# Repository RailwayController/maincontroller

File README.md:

<!--
SPDX-FileCopyrightText: 2022 Sidings Media <contact@sidingsmedia.com>
SPDX-License-Identifier: CC-BY-SA-4.0
-->

# Railway Controller - Main control board

The main control board is the central control node of the railway controller
system. The main control board controls all aspects of the system, from handling
user inputs to sending commands to the control nodes.

The board is based upon the RP2040 and can either be fitted with a Raspberry Pi
Pico board or use the RP2040 chip on it's own with all the required supporting
circuitry being implemented on the board it's self. The board is designed to fit
inside a standard 3U eurocard enclosure with a depth of 160mm and a height of
100mm. The rear connector provides connectivity to the backplane to allow
communication between all nodes in the rack as well as to supply power to the
board.

The PCBs have been designed with 2 layers and with SMD components that should be
possible to hand solder with a small tip and some practice. An important note,
the boards have been designed acording to JLCPCB's design constraints, if you
are ordering from a different manufacturer, it is a good idea to make sure that
they support the same or better constraints.

This repository contains designs for the main controller board for
use with the railway controller system. Rendered versions of the schematics, for
example schematics in the PDF format, are included with the releases. Gerber
files are also included with releases. These have been generated to work with
JLCPCB but they should work with most other board manufacturers. 

## Licence
This repo uses the [REUSE](https://reuse.software) standard in order to
communicate the correct licence for the file. For those unfamiliar with
the standard the licence for each file can be found in one of three
places. The licence will either be in a comment block at the top of the
file, in a `.license` file with the same name as the file, or in the
dep5 file located in the `.reuse` directory. If you are unsure of the
licencing terms please contact
[contact@sidingsmedia.com](mailto:contact@sidingsmedia.com?subject=Railway%20Controller%20Licence).
All files committed to this repo must contain valid licencing
information or the pull request can not be accepted.

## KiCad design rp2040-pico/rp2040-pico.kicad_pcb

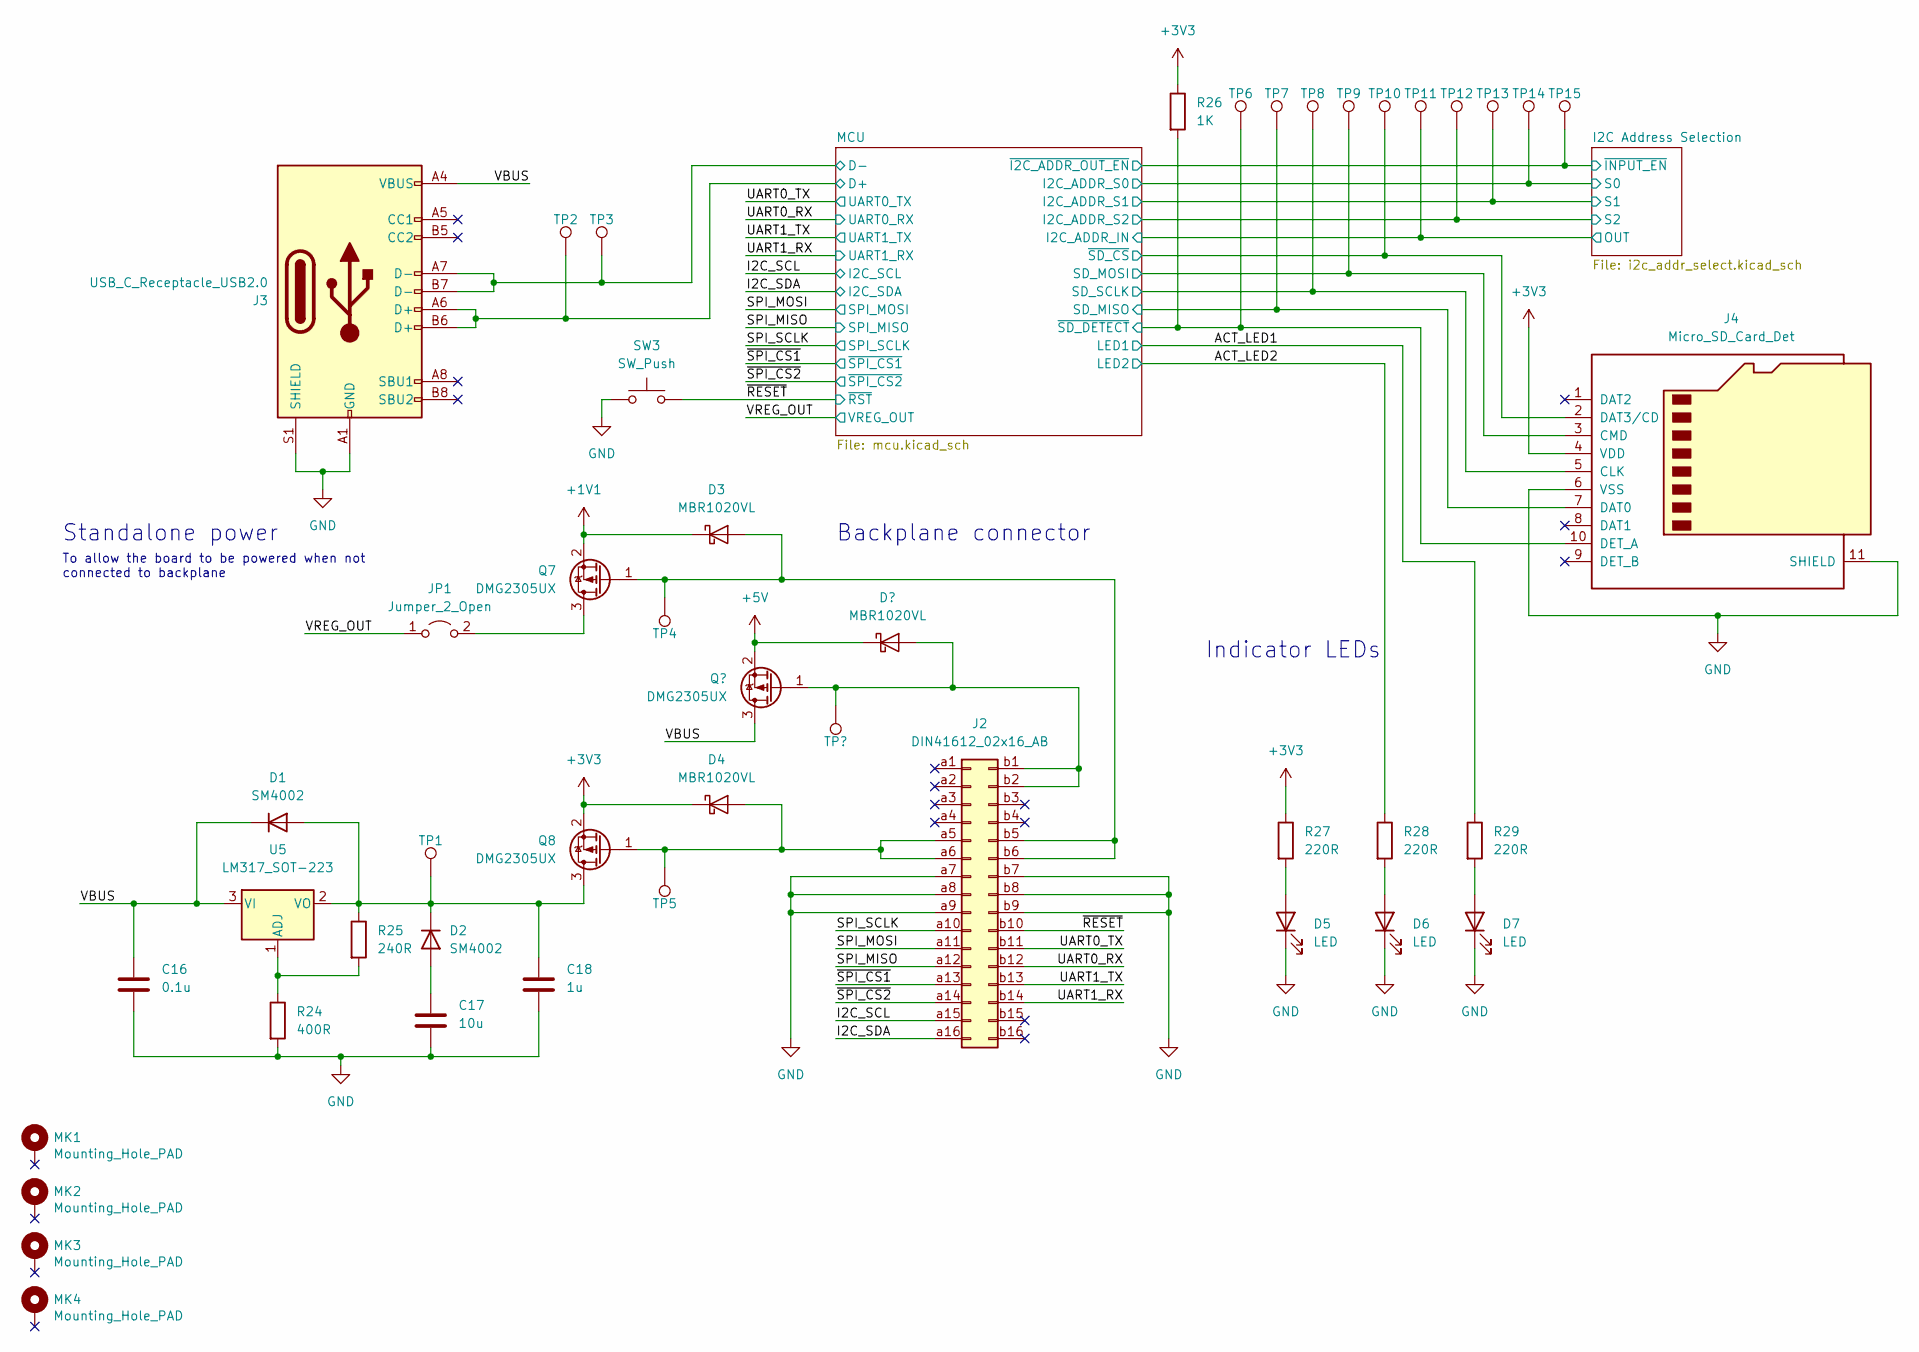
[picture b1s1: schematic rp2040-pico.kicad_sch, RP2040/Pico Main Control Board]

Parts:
C16: 0.1u; C_0402_1005Metric_Pad0.74x0.62mm_HandSolder
C17: 10u; C_0402_1005Metric_Pad0.74x0.62mm_HandSolder
C18: 1u; C_0402_1005Metric_Pad0.74x0.62mm_HandSolder
D1, D2: SM4002; D_MELF
D3, D4: MBR1020VL; D_SOD-123F
D5, D6, D7: LED; LED_0603_1608Metric_Pad1.05x0.95mm_HandSolder
J2: DIN41612_02x16_AB; DIN41612_B2_2x16_Male_Horizontal_THT
J3: USB_C_Receptacle_USB2.0; USB_C_Receptacle_Palconn_UTC16-G
J4: Micro_SD_Card_Det; microSD_HC_Molex_104031-0811
JP1: Jumper_2_Open; SolderJumper-2_P1.3mm_Open_Pad1.0x1.5mm
MK1, MK2, MK3, MK4: Mounting_Hole_PAD; MountingHole_2.7mm
Q7, Q8: DMG2305UX; SOT-23
R24: 400R; R_0402_1005Metric_Pad0.72x0.64mm_HandSolder
R25: 240R; R_0402_1005Metric_Pad0.72x0.64mm_HandSolder
R26: 1K; R_0402_1005Metric_Pad0.72x0.64mm_HandSolder
R27, R28, R29: 220R; R_0402_1005Metric_Pad0.72x0.64mm_HandSolder
SW3: SW_Push; SW_SPST_B3U-1000P
TP1, TP2, TP3, TP4, TP5, TP6, TP7, TP8, TP9, TP10, TP11, TP12, TP13, TP14, TP15: TestPoint; TestPoint_Pad_D1.0mm
U5: LM317_SOT-223; SOT-223-3_TabPin2

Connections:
+1V1: D3.1 (K), Q7.2 (S); also elsewhere on the board
+3V3: D4.1 (K), J4.4 (VDD), Q8.2 (S), R26.1, R27.1; also elsewhere on the board
/ACT_LED1: R29.1; also elsewhere on the board
/ACT_LED2: R28.1; also elsewhere on the board
/I2C Address Selection/OUT: TP11.1; also elsewhere on the board
/I2C Address Selection/S0: TP14.1; also elsewhere on the board
/I2C Address Selection/S1: TP13.1; also elsewhere on the board
/I2C Address Selection/S2: TP12.1; also elsewhere on the board
/I2C Address Selection/~INPUT_EN: TP15.1; also elsewhere on the board
/I2C_SCL: J2.a15; also elsewhere on the board
/I2C_SDA: J2.a16; also elsewhere on the board
/MCU/D+: J3.A6 (D+), J3.B6 (D+), TP2.1; also elsewhere on the board
/MCU/D-: J3.A7 (D-), J3.B7 (D-), TP3.1; also elsewhere on the board
/MCU/SD_MISO: J4.7 (DAT0), TP7.1; also elsewhere on the board
/MCU/SD_MOSI: J4.3 (CMD), TP9.1; also elsewhere on the board
/MCU/SD_SCLK: J4.5 (CLK), TP8.1; also elsewhere on the board
/MCU/~SD_CS: J4.2 (DAT3/CD), TP10.1; also elsewhere on the board
/MCU/~SD_DETECT: J4.10 (DET_A), R26.2, TP6.1; also elsewhere on the board
/SPI_MISO: J2.a12; also elsewhere on the board
/SPI_MOSI: J2.a11; also elsewhere on the board
/SPI_SCLK: J2.a10; also elsewhere on the board
/UART0_RX: J2.b12; also elsewhere on the board
/UART0_TX: J2.b11; also elsewhere on the board
/UART1_RX: J2.b14; also elsewhere on the board
/UART1_TX: J2.b13; also elsewhere on the board
/VBUS: C16.1, D1.1 (K), J3.A4 (VBUS), J3.A9 (VBUS), J3.B4 (VBUS), J3.B9 (VBUS), U5.3 (VI); also elsewhere on the board
/VREG_OUT: JP1.1 (A); also elsewhere on the board
/~RESET: J2.b10, SW3.2; also elsewhere on the board
/~SPI_CS1: J2.a13; also elsewhere on the board
/~SPI_CS2: J2.a14; also elsewhere on the board
GND: C16.2, C17.2, C18.2, D5.1 (K), D6.1 (K), D7.1 (K), J2.a7, J2.a8, J2.a9, J2.b7, J2.b8, J2.b9, J3.A1 (GND), J3.A12 (GND), J3.B1 (GND), J3.B12 (GND), J3.S1 (SHIELD), J4.6 (VSS), J4.11 (SHIELD), R24.2, SW3.1; also elsewhere on the board
unnamed: C17.1, D2.2 (A)
unnamed: C18.1, D1.2 (A), D2.1 (K), Q8.3 (D), R25.1, TP1.1, U5.2 (VO)
unnamed: D3.2 (A), J2.b5, J2.b6, Q7.1 (G), TP4.1
unnamed: D4.2 (A), J2.a5, J2.a6, Q8.1 (G), TP5.1
unnamed: D5.2 (A), R27.2
unnamed: D6.2 (A), R28.2
unnamed: D7.2 (A), R29.2
unnamed 51: J2.b1, J2.b2; also elsewhere on the board
unnamed: JP1.2 (B), Q7.3 (D)
unnamed: R24.1, R25.2, U5.1 (ADJ)

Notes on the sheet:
To allow the board to be powered when not connected to backplane
Backplane connector
Standalone power
Indicator LEDs

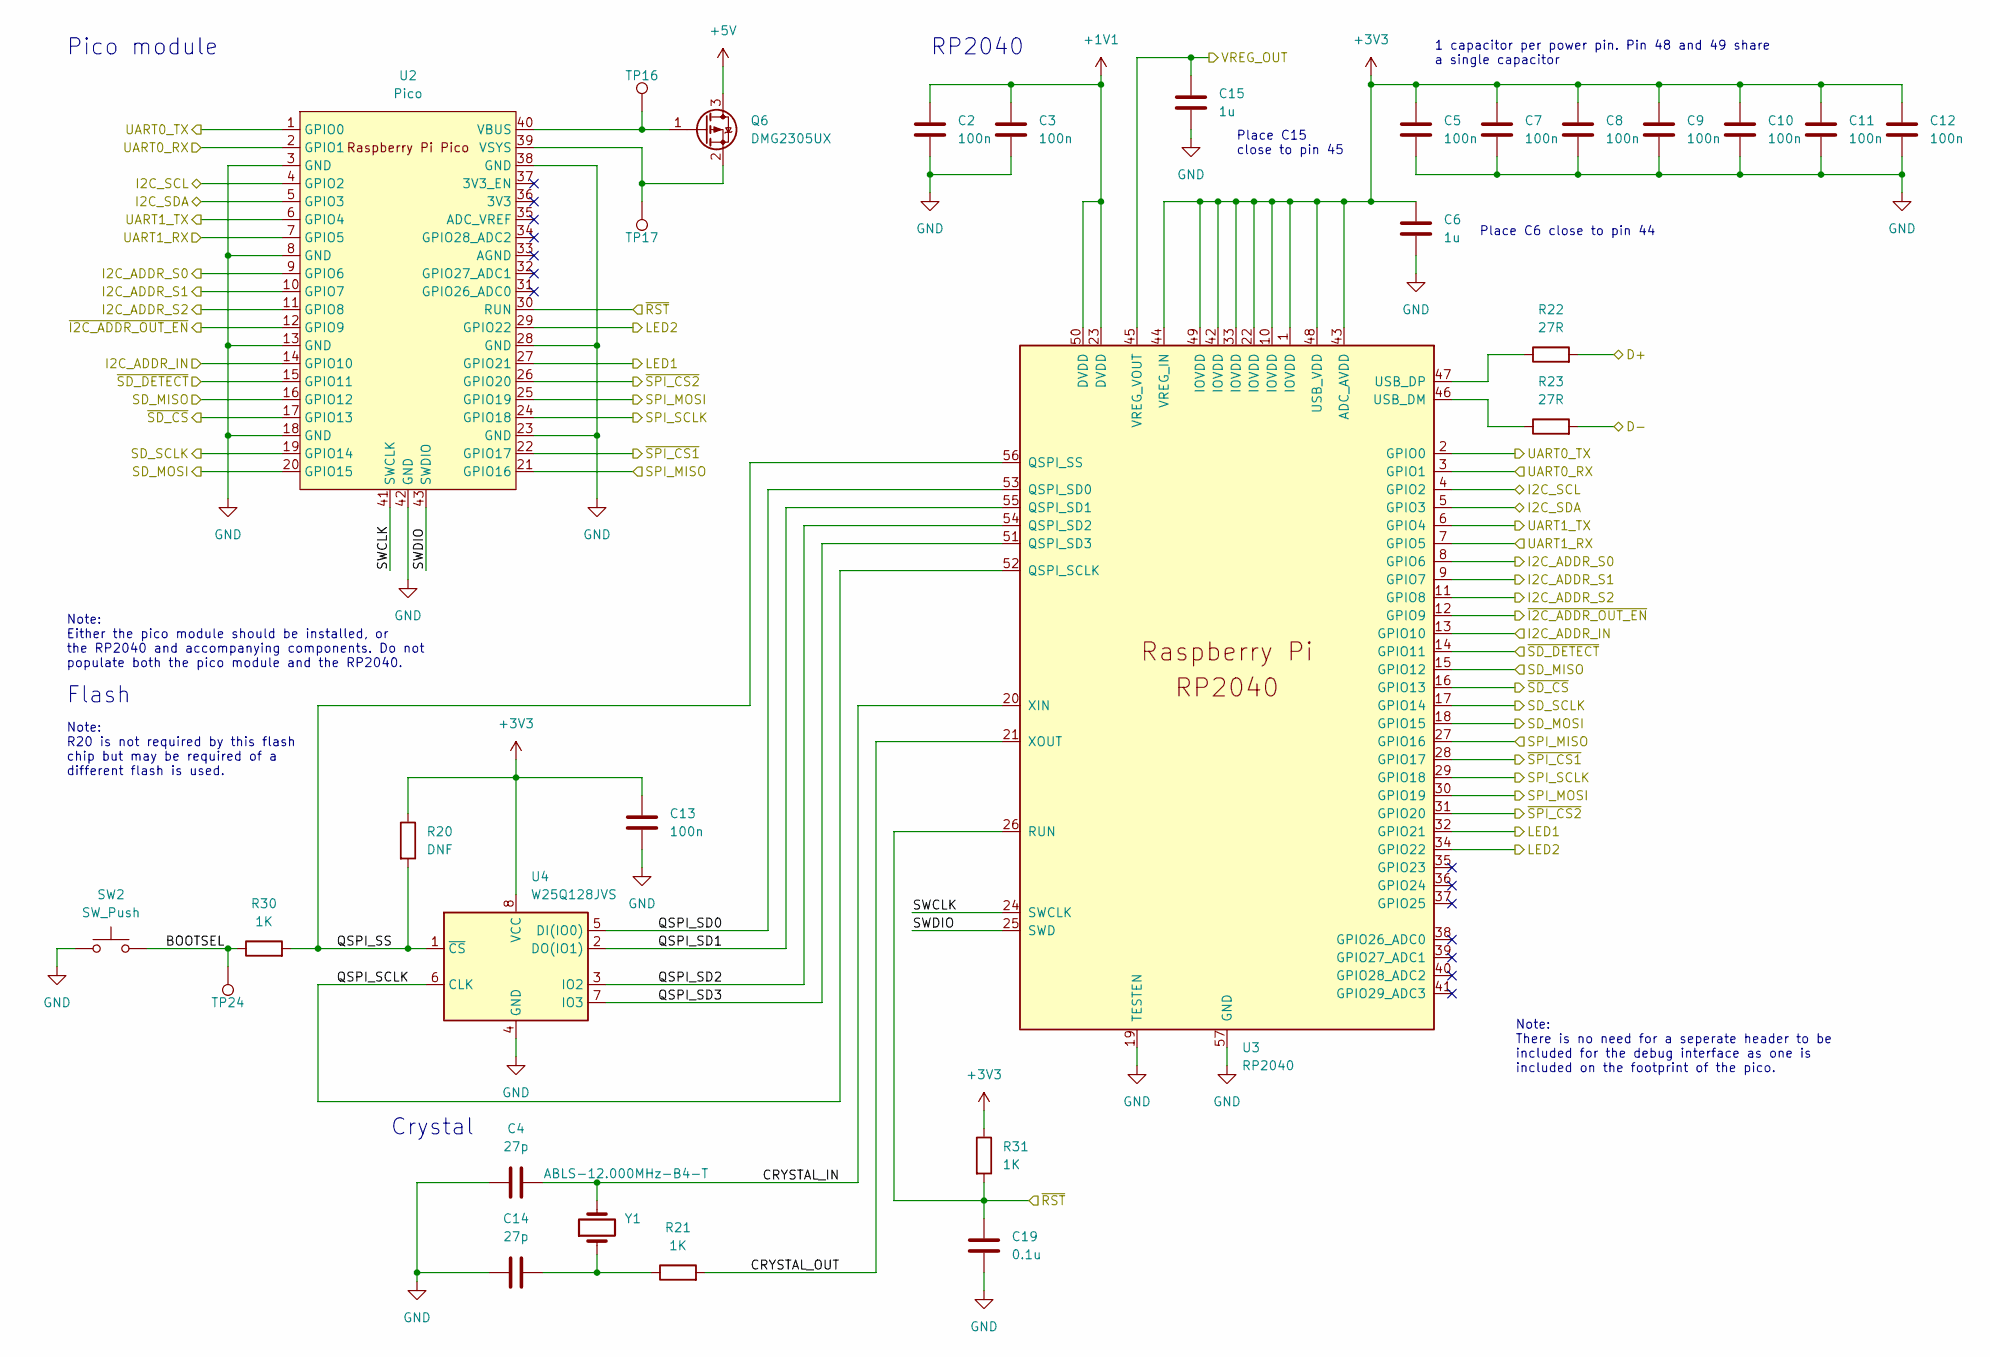
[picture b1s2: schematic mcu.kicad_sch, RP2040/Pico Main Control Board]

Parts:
C2, C3, C5, C7, C8, C9, C10, C11, C12, C13: 100n; C_0402_1005Metric_Pad0.74x0.62mm_HandSolder
C4, C14: 27p; C_0402_1005Metric_Pad0.74x0.62mm_HandSolder
C6, C15: 1u; C_0402_1005Metric_Pad0.74x0.62mm_HandSolder
C19: 0.1u; C_0402_1005Metric_Pad0.74x0.62mm_HandSolder
Q6: DMG2305UX; SOT-23
R20: DNF; R_0402_1005Metric_Pad0.72x0.64mm_HandSolder
R21, R30, R31: 1K; R_0402_1005Metric_Pad0.72x0.64mm_HandSolder
R22, R23: 27R; R_0402_1005Metric_Pad0.72x0.64mm_HandSolder
SW2: SW_Push; SW_SPST_B3U-1000P
TP16, TP17, TP24: TestPoint; TestPoint_Pad_D1.0mm
U2: Pico; RPi_Pico_SMD_TH
U3: RP2040; RP2040-QFN-56
U4: W25Q128JVS; SOIC-8_5.23x5.23mm_P1.27mm
Y1: ABLS-12.000MHz-B4-T; Crystal_SMD_HC49-SD_HandSoldering

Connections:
+1V1: C2.1, C3.1, U3.23 (DVDD), U3.50 (DVDD); also elsewhere on the board
+3V3: C5.1, C6.1, C7.1, C8.1, C9.1, C10.1, C11.1, C12.1, C13.1, R20.1, R31.1, U3.1 (IOVDD), U3.10 (IOVDD), U3.22 (IOVDD), U3.33 (IOVDD), U3.42 (IOVDD), U3.43 (ADC_AVDD), U3.44 (VREG_IN), U3.48 (USB_VDD), U3.49 (IOVDD), U4.8 (VCC); also elsewhere on the board
+5V: Q6.3 (D); also elsewhere on the board
/ACT_LED1: U2.27 (GPIO21), U3.32 (GPIO21); also elsewhere on the board
/ACT_LED2: U2.29 (GPIO22), U3.34 (GPIO22); also elsewhere on the board
/I2C Address Selection/OUT: U2.14 (GPIO10), U3.13 (GPIO10); also elsewhere on the board
/I2C Address Selection/S0: U2.9 (GPIO6), U3.8 (GPIO6); also elsewhere on the board
/I2C Address Selection/S1: U2.10 (GPIO7), U3.9 (GPIO7); also elsewhere on the board
/I2C Address Selection/S2: U2.11 (GPIO8), U3.11 (GPIO8); also elsewhere on the board
/I2C Address Selection/~INPUT_EN: U2.12 (GPIO9), U3.12 (GPIO9); also elsewhere on the board
/I2C_SCL: U2.4 (GPIO2), U3.4 (GPIO2); also elsewhere on the board
/I2C_SDA: U2.5 (GPIO3), U3.5 (GPIO3); also elsewhere on the board
/MCU/BOOTSEL: R30.1, SW2.2, TP24.1
/MCU/CRYSTAL_IN: C4.2, U3.20 (XIN), Y1.2
/MCU/CRYSTAL_OUT: R21.2, U3.21 (XOUT)
/MCU/D+: R22.2; also elsewhere on the board
/MCU/D-: R23.2; also elsewhere on the board
/MCU/QSPI_SCLK: U3.52 (QSPI_SCLK), U4.6 (CLK)
/MCU/QSPI_SD0: U3.53 (QSPI_SD0), U4.5 (DI(IO0))
/MCU/QSPI_SD1: U3.55 (QSPI_SD1), U4.2 (DO(IO1))
/MCU/QSPI_SD2: U3.54 (QSPI_SD2), U4.3 (IO2)
/MCU/QSPI_SD3: U3.51 (QSPI_SD3), U4.7 (IO3)
/MCU/QSPI_SS: R20.2, R30.2, U3.56 (QSPI_SS), U4.1 (~CS)
/MCU/SD_MISO: U2.16 (GPIO12), U3.15 (GPIO12); also elsewhere on the board
/MCU/SD_MOSI: U2.20 (GPIO15), U3.18 (GPIO15); also elsewhere on the board
/MCU/SD_SCLK: U2.19 (GPIO14), U3.17 (GPIO14); also elsewhere on the board
/MCU/SWCLK: U2.41 (SWCLK), U3.24 (SWCLK)
/MCU/SWDIO: U2.43 (SWDIO), U3.25 (SWD)
/MCU/~SD_CS: U2.17 (GPIO13), U3.16 (GPIO13); also elsewhere on the board
/MCU/~SD_DETECT: U2.15 (GPIO11), U3.14 (GPIO11); also elsewhere on the board
/SPI_MISO: U2.21 (GPIO16), U3.27 (GPIO16); also elsewhere on the board
/SPI_MOSI: U2.25 (GPIO19), U3.30 (GPIO19); also elsewhere on the board
/SPI_SCLK: U2.24 (GPIO18), U3.29 (GPIO18); also elsewhere on the board
/UART0_RX: U2.2 (GPIO1), U3.3 (GPIO1); also elsewhere on the board
/UART0_TX: U2.1 (GPIO0), U3.2 (GPIO0); also elsewhere on the board
/UART1_RX: U2.7 (GPIO5), U3.7 (GPIO5); also elsewhere on the board
/UART1_TX: U2.6 (GPIO4), U3.6 (GPIO4); also elsewhere on the board
/VREG_OUT: C15.1, U3.45 (VREG_VOUT); also elsewhere on the board
/~RESET: C19.1, R31.2, U2.30 (RUN), U3.26 (RUN); also elsewhere on the board
/~SPI_CS1: U2.22 (GPIO17), U3.28 (GPIO17); also elsewhere on the board
/~SPI_CS2: U2.26 (GPIO20), U3.31 (GPIO20); also elsewhere on the board
GND: C2.2, C3.2, C4.1, C5.2, C6.2, C7.2, C8.2, C9.2, C10.2, C11.2, C12.2, C13.2, C14.1, C15.2, C19.2, SW2.1, U2.3 (GND), U2.8 (GND), U2.13 (GND), U2.18 (GND), U2.23 (GND), U2.28 (GND), U2.38 (GND), U2.42 (GND), U3.19 (TESTEN), U3.57 (GND), U4.4 (GND); also elsewhere on the board
unnamed: C14.2, R21.1, Y1.1
unnamed: Q6.1 (G), TP16.1, U2.40 (VBUS)
unnamed: Q6.2 (S), TP17.1, U2.39 (VSYS)
unnamed: R22.1, U3.47 (USB_DP)
unnamed: R23.1, U3.46 (USB_DM)

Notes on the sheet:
Flash
Pico module
Place C15 close to pin 45
1 capacitor per power pin. Pin 48 and 49 share a single capacitor
Note: Either the pico module should be installed, or the RP2040 and accompanying components. Do not populate both the pico module and the RP2040.
Note: There is no need for a seperate header to be included for the debug interface as one is included on the footprint of the pico.
Place C6 close to pin 44
Crystal
RP2040
Note: R20 is not required by this flash chip but may be required of a different flash is used.

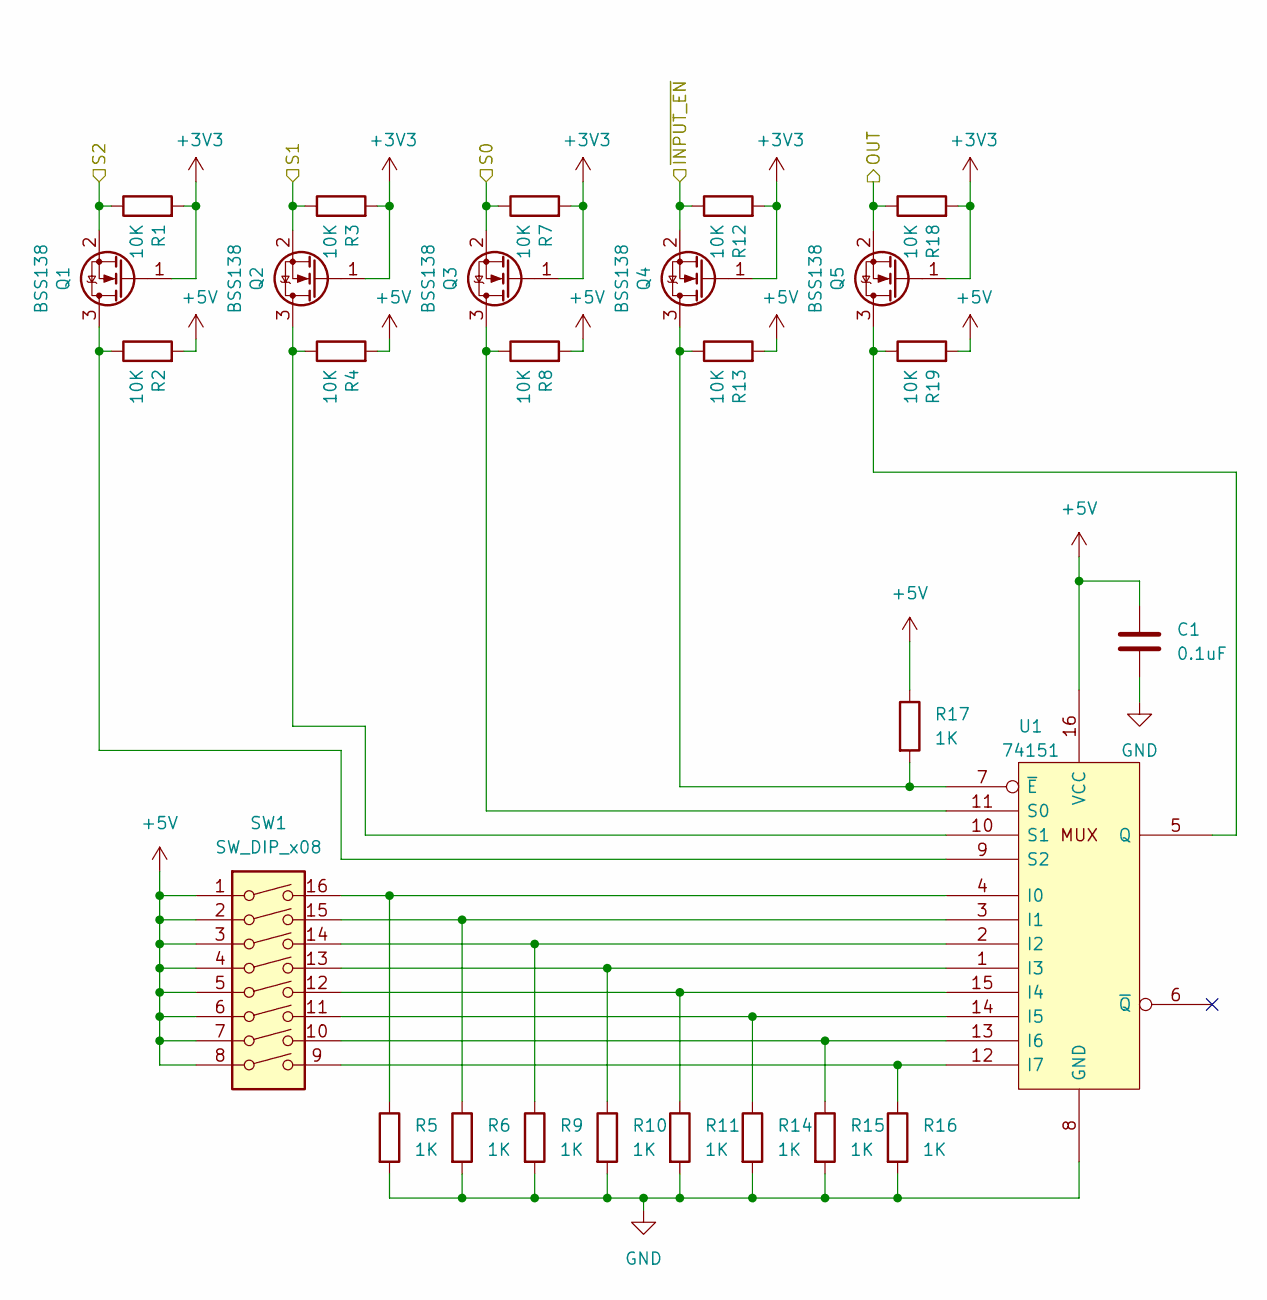
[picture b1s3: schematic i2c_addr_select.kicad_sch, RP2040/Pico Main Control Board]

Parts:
C1: 0.1uF; C_0402_1005Metric_Pad0.74x0.62mm_HandSolder
Q1, Q2, Q3, Q4, Q5: BSS138; SOT-23
R1, R2, R3, R4, R7, R8, R12, R13, R18, R19: 10K; R_0402_1005Metric_Pad0.72x0.64mm_HandSolder
R5, R6, R9, R10, R11, R14, R15, R16, R17: 1K; R_0402_1005Metric_Pad0.72x0.64mm_HandSolder
SW1: SW_DIP_x08; SW_DIP_SPSTx08_Slide_6.7x21.88mm_W7.62mm_P2.54mm_LowProfile
U1: 74151; SOIC-16_3.9x9.9mm_P1.27mm

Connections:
+3V3: Q1.1 (G), Q2.1 (G), Q3.1 (G), Q4.1 (G), Q5.1 (G), R1.2, R3.2, R7.2, R12.2, R18.2; also elsewhere on the board
+5V: C1.1, R2.2, R4.2, R8.2, R13.2, R17.1, R19.2, SW1.1, SW1.2, SW1.3, SW1.4, SW1.5, SW1.6, SW1.7, SW1.8, U1.16 (VCC); also elsewhere on the board
/I2C Address Selection/OUT: Q5.2 (S), R18.1; also elsewhere on the board
/I2C Address Selection/S0: Q3.2 (S), R7.1; also elsewhere on the board
/I2C Address Selection/S1: Q2.2 (S), R3.1; also elsewhere on the board
/I2C Address Selection/S2: Q1.2 (S), R1.1; also elsewhere on the board
/I2C Address Selection/~INPUT_EN: Q4.2 (S), R12.1; also elsewhere on the board
GND: C1.2, R5.2, R6.2, R9.2, R10.2, R11.2, R14.2, R15.2, R16.2, U1.8 (GND); also elsewhere on the board
unnamed: Q1.3 (D), R2.1, U1.9 (S2)
unnamed: Q2.3 (D), R4.1, U1.10 (S1)
unnamed: Q3.3 (D), R8.1, U1.11 (S0)
unnamed: Q4.3 (D), R13.1, R17.2, U1.7 (~E)
unnamed: Q5.3 (D), R19.1, U1.5 (Q)
unnamed: R5.1, SW1.16, U1.4 (I0)
unnamed: R6.1, SW1.15, U1.3 (I1)
unnamed: R9.1, SW1.14, U1.2 (I2)
unnamed: R10.1, SW1.13, U1.1 (I3)
unnamed: R11.1, SW1.12, U1.15 (I4)
unnamed: R14.1, SW1.11, U1.14 (I5)
unnamed: R15.1, SW1.10, U1.13 (I6)
unnamed: R16.1, SW1.9, U1.12 (I7)

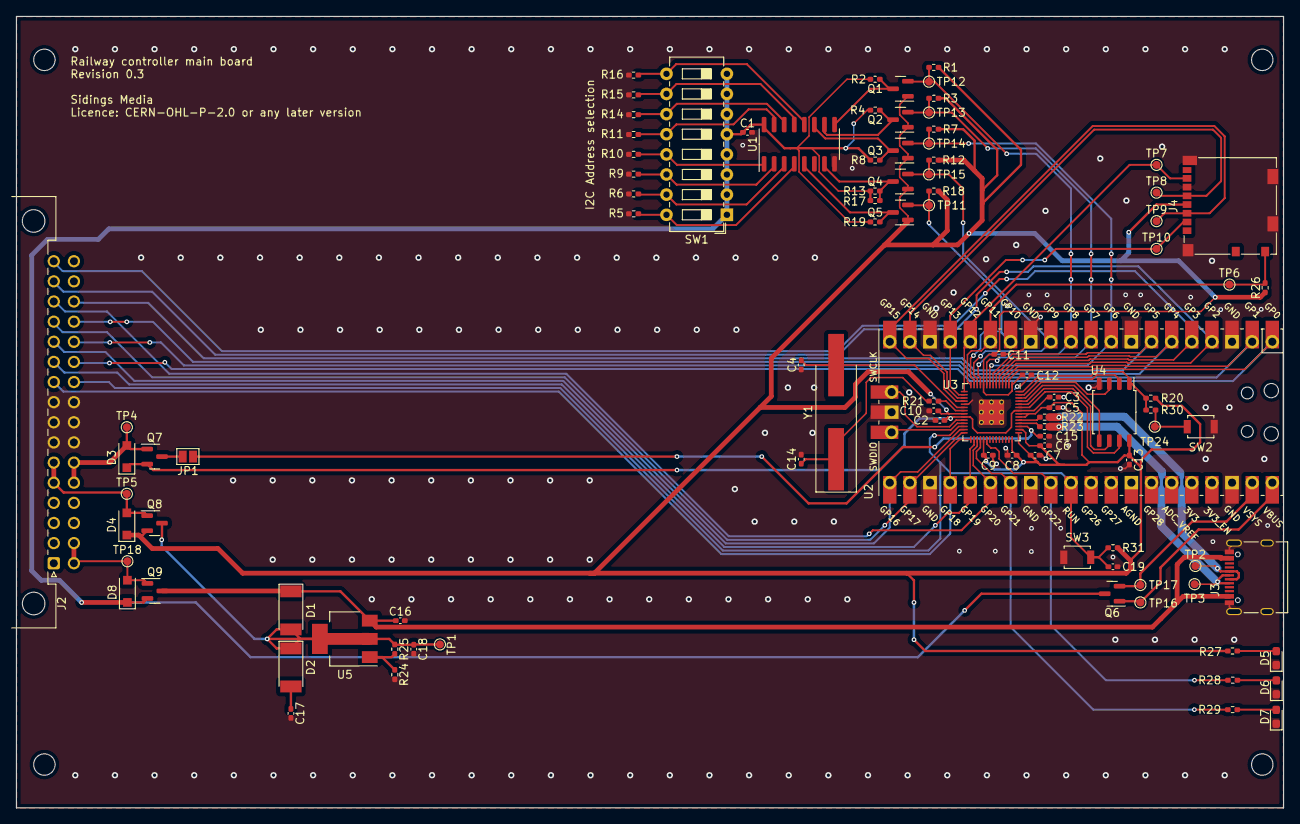
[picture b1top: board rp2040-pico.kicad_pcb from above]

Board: 2 copper layers, 159.9 x 99.9 mm, 103 parts (0 on the bottom side), 71 nets.

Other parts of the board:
D8: MBR1020VL; D_SOD-123F
Q9: DMG2305UX; SOT-23
TP18: TestPoint; TestPoint_Pad_D1.0mm

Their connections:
+5V: D8.1 (K), Q9.2 (S); also elsewhere on the board
/VBUS: Q9.3 (D); also elsewhere on the board
unnamed 51: D8.2 (A), Q9.1 (G), TP18.1; also elsewhere on the board

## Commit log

2022-11-18 Updated README to match repo
2022-11-18 Initialized KiCad Project
2022-11-18 Fixed reuse + updated schematic template
    Reuse compatability has been fixed by updating the dep5 file.
    Also updated template for schematic and filled in schematic info
    fields.
2022-11-18 Initial board design
    The initial design for the Rasbperry Pi Pico based board.
2022-11-20 Updated RP2040 schematic to include RP2040 + Pico
    The schematic has been updated to now include the option to either use a
    raspberry pi pico module, or to use an RP2040.
2022-11-20 Added stat LEDs, BOOTSEL and reset button, SD card
    3 LEDs have been added. One for indicating power and two for indicating
    activity. Both activity LEDs are currently connected to the Pico/RP2040.
    Buttons for boot selection and chip reset have been added to allow for
    loading of firmware over USB. Support for a micro SD has also been
    added. The card communicates with the Pico/RP2040 via the MCUs second
    SPI interface and will store config files.
2022-11-20 Changed LM317 decoupling caps to non polarized
    There is no need for C16, C17 or C18 to be polarized capacitors. As
    such, they have been changed to be non polarized.
2022-11-20 Assigned value to C19
2022-11-20 Added device footprints
2022-11-20 Updated schematic and started PCB development
    Test points have been removed from the schematic where they were found
    to be unnecessary or would make efficient placement of components
    impossible. Most notable the test points connected to the flash chip.
    These are not required as one can just probe the pins of the flash chip
    with ease.
    Some nets have also been labeled to assist in PCB development.
2022-11-26 Added rev 0.3 PCB + minor alterations to schematic
    The PCB design work has been completed for rev 0.3 of the board. Some
    minor changes to the schematic were made as issues were encountered
    during board design. The most notable being the removal of unneccessary
    test points and the addition of another P-channel mosfet to allow the 5V
    rail to have two seperate power supplies.
2022-11-26 Rendered schematic for rev 0.3
2022-11-26 Added interactive BOM for rev 0.3
2022-11-26 Switched pour mode to full connections
    Previously the fill mode was set to use thermal reliefs, however this
    led to some vias not being properly connected.
2022-11-26 Removed generated files
    Removed generated files as these are to be included with the release
    instead.
2022-11-26 Added more descriptive readme + images
2022-11-26 Fixed reuse compliance
2022-11-26 Some minor changes and increment version number
2022-11-27 Minor changes to UUIDs

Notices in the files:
rp2040-pico/i2c_addr_select.kicad_sch:
Licence: CERN-OHL-P-2.0 or any later version
